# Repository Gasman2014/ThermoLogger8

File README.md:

# ThermoLogger8

Just quickly pushed this repo if anyone is interested. It works in bradboard format and I have designed a PCB in KiCad. There is a 5v and 
a 3.3v version depending on choice of MC. I have been using Fosil as a VCS for this project and have just pushed the whole repo to GitHub.
If you are interested in the development history I could add the Fossil.repo.

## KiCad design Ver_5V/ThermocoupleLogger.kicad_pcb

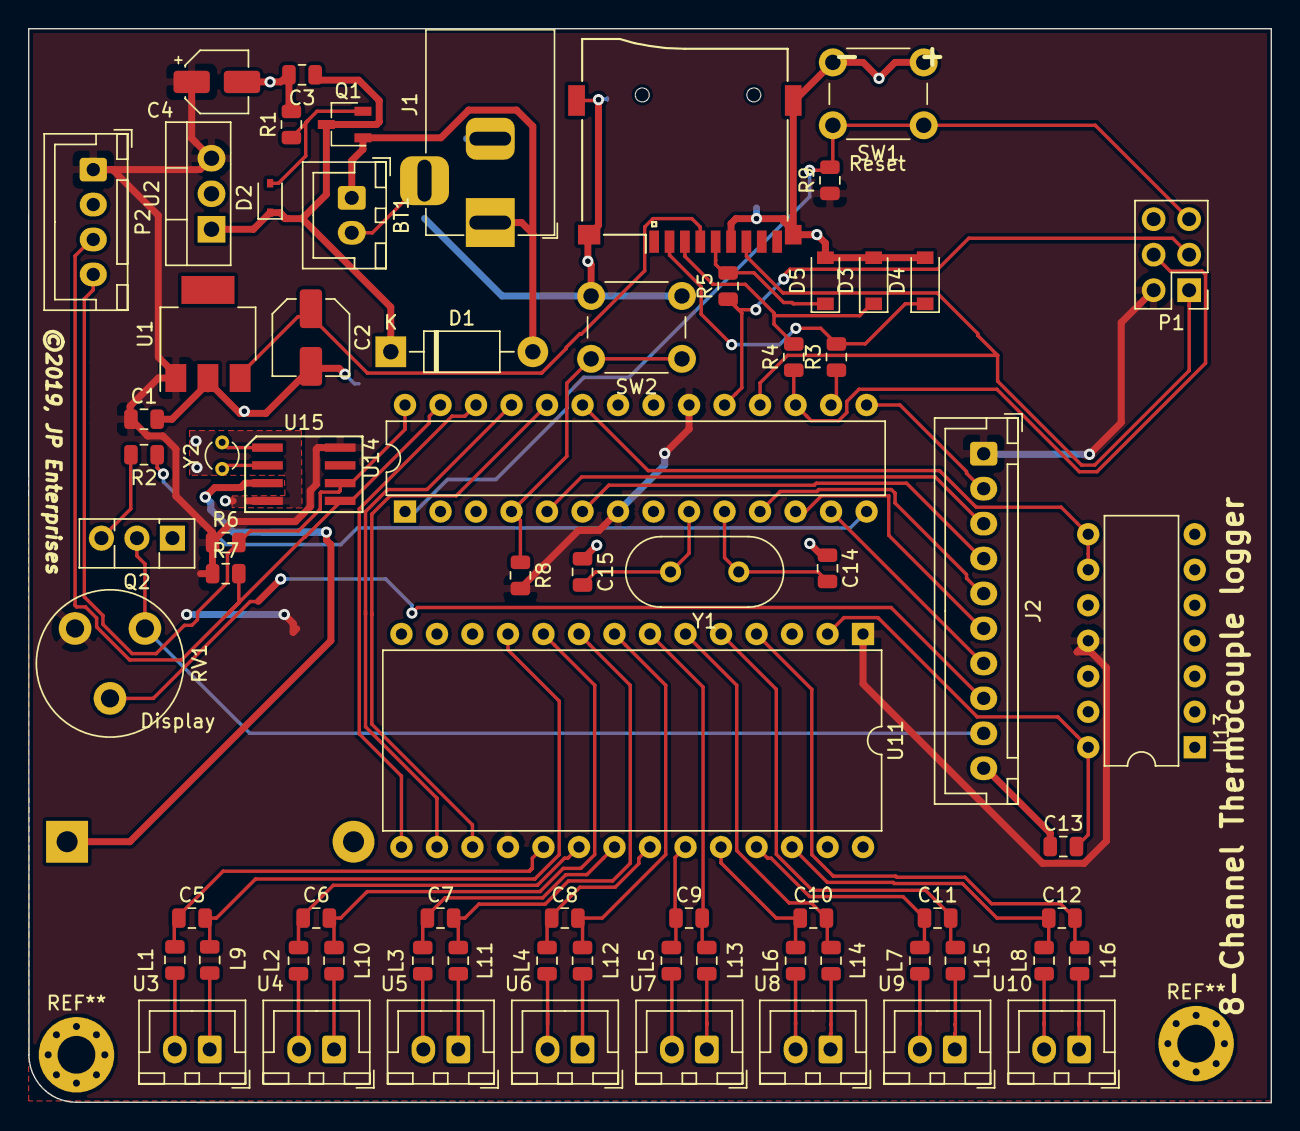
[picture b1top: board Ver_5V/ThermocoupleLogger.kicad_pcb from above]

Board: 2 copper layers, 88.9 x 76.8 mm, 73 parts (1 on the bottom side), 70 nets.

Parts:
BT1: 9V; JST_XH_B02B-XH-A_1x02_P2.50mm_Vertical
BT2: Battery; BatteryHolder_Keystone_103_1x20mm
C1: 470nF; C_0805_2012Metric
C2: 47uF; C_Elec_5x5.4
C3: 1uF; C_0805_2012Metric
C4: 10uF; CP_Elec_4x5.4
C5, C6, C7, C8, C9, C10, C11, C12, C13: 10nF; C_0805_2012Metric
C14, C15: 18pF; C_0805_2012Metric
D1: 1N4007; D_DO-41_SOD81_P10.16mm_Horizontal
D2: 9V; D_SOD-323
D3, D4, D5: 3.3V; D_SOD-123
J1: Barrel_Jack; BarrelJack_Horizontal
J2: Conn_01x12_Male; JST_XH_B10B-XH-A_1x10_P2.50mm_Vertical
L1, L2, L3, L4, L5, L6, L7, L8, L9, L10, L11, L12, L13, L14, L15, L16: 150; L_0805_2012Metric
P1: CONN_02X03; PinHeader_2x03_P2.54mm_Vertical
P2: Conn_01x04; JST_XH_B04B-XH-A_1x04_P2.50mm_Vertical
Q1: BS250; TSOT-23
Q2: BD139; TO-126-3_Vertical
R1, R2, R6, R7, R8, R9: 10K; R_0805_2012Metric
R3, R4, R5: 220R; R_0805_2012Metric
RV1: 5k; Potentiometer_Piher_PT-10-V05_Vertical
SW1, SW2: SW_Push; SW_PUSH_6mm_H5mm
U1: LM3940; SOT-223
U2: 7805; TO-220-3_Vertical
U3, U4, U5, U6, U7, U8, U9, U10: TC_Connector; JST_XH_B02B-XH-A_1x02_P2.50mm_Vertical
U11: ADG407; DIP-28_W15.24mm
U13: AD595; DIP-14_W7.62mm
U14: ATMEGA328P-PU; DIP-28_W7.62mm
U15: DS1307+; DS1307
XS1: SD_ebay-uSD-push/push_SMD; Conn_uSDcard
Y1: 16MHz; Crystal_HC49-U_Vertical
Y2: 32.768kHz; Crystal_DS26_D2.0mm_L6.0mm_Vertical

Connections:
3V3: C2.1, U1.3, XS1.4
5V0: C1.1, C4.1, J2.1, P1.2, P2.1, R6.1, R7.1, R8.2, R9.1, RV1.1, U1.1, U2.3, U11.1, U11.18, U13.11, U14.7, U14.20, U15.8
9V0: C3.1, D1.1, D2.1, Q1.3, U2.1
/Thermocouple connectors/SA1: C5.1, L1.1, U11.19
/Thermocouple connectors/SA2: C6.1, L2.1, U11.20
/Thermocouple connectors/SA3: C7.1, L3.1, U11.21
/Thermocouple connectors/SA4: C8.1, L4.1, U11.22
/Thermocouple connectors/SA5: C9.1, L5.1, U11.23
/Thermocouple connectors/SA6: C10.1, L6.1, U11.24
/Thermocouple connectors/SA7: C11.1, L7.1, U11.25
/Thermocouple connectors/SA8: C12.1, L8.1, U11.26
/Thermocouple connectors/SB1: C5.2, L9.2, U11.11
/Thermocouple connectors/SB2: C6.2, L10.2, U11.10
/Thermocouple connectors/SB3: C7.2, L11.2, U11.9
/Thermocouple connectors/SB4: C8.2, L12.2, U11.8
/Thermocouple connectors/SB5: C9.2, L13.2, U11.7
/Thermocouple connectors/SB6: C10.2, L14.2, U11.6
/Thermocouple connectors/SB7: C11.2, L15.2, U11.5
/Thermocouple connectors/SB8: C12.2, L16.2, U11.4
B_LIGHT: R2.1, U14.14
DB4: J2.4, U14.6
DB5: J2.5, U14.11
DB6: J2.6, U14.12
DB7: J2.7, U14.13
DB_MUX: C13.2, U11.2, U13.14
EN: J2.3, U14.5
GND: BT2.2, C1.2, C2.2, C3.2, C4.2, C13.1, C14.1, C15.1, D3.2, D4.2, D5.2, J1.2, J2.10, P1.6, P2.2, Q2.1, R1.2, SW1.2, SW2.2, U1.2, U2.2, U11.12, U11.28, U13.1, U13.4, U13.7, U13.13, U14.8, U14.22, U15.4, XS1.6
MISO: P1.1, U14.18, XS1.7
MOSI: P1.4, R4.1, U14.17
unnamed: BT1.2, J1.3
unnamed: BT2.1, U15.3
unnamed: C14.2, U14.10, Y1.1
unnamed: C15.2, U14.9, Y1.2
unnamed: D2.2, Q1.2, R1.1
unnamed: D3.1, R4.2, XS1.3
unnamed: D4.1, R3.2, XS1.2
unnamed: D5.1, R5.2, XS1.5
unnamed: J2.8, RV1.2
unnamed: J2.9, Q2.2, RV1.3
unnamed: L1.2, U3.2
unnamed: L2.2, U4.2
unnamed: L3.2, U5.2
unnamed: L4.2, U6.2
unnamed: L5.2, U7.2
unnamed: L6.2, U8.2
unnamed: L7.2, U9.2
unnamed: L8.2, U10.2
unnamed: L9.1, U3.1
unnamed: L10.1, U4.1
unnamed: L11.1, U5.1
unnamed: L12.1, U6.1
unnamed: L13.1, U7.1
unnamed: L14.1, U8.1
unnamed: L15.1, U9.1
unnamed: L16.1, U10.1
unnamed: Q2.3, R2.2
unnamed: U15.1, Y2.2
unnamed: U15.2, Y2.1
RESET: P1.5, R9.2, SW1.1, U14.1
RS: J2.2, U14.15
SCK: P1.3, R5.1, U14.19
SCL: P2.4, R6.2, U14.28, U15.6
SDA: P2.3, R7.2, U14.27, U15.5
SELCT: R8.1, SW2.1, U14.4
SLCT0: U11.17, U14.24
SLCT1: U11.16, U14.25
SLCT2: U11.15, U14.26
SS: R3.1, U14.16
SUPPLY: BT1.1, D1.2, J1.1, Q1.1
TEMP: U13.8, U13.9, U14.23

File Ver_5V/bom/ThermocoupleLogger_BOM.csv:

Component,Description,Part,References,Value,Footprint,Quantity Per PCB,Datasheet,Part#,Placement,Package_ID,Characteristics
1,-,Battery-device,BT1,9V,JST_XH_B02B-XH-A_02x2.50mm_Straight,1,/Users/johnpateman/Dropbox/Components/Datasheets/connectors/eXH.pdf,B2B-XH-A,-,-,-
2,-,Battery_Cell-device,BT2,Battery,Keystone_103_1x20mm-CoinCell,1,,KEYSTONE 103,-,-,-
3,-,C_Small-device,C5 C6 C7 C8 C9 C10 C11 C12 C13,10nF,C_0805,9,,-,-,-,X7R -
4,-,CP_Small,C4,10uF,CP_Elec_4x5.4,1,,EEEFK1C100R,-,-,-
5,-,C_Small-device,C16 C17,12pF,C_0805,2,,-,-,-,-
6,-,C_Small-device,C14 C15,18pF,C_0805,2,,-,-,-,-
7,-,C_Small,C3,1uF,C_0805,1,,-,-,-,-
8,-,C_Small-device,C1,470nF,C_0805,1,,-,-,-,X7R
9,-,CP_Small-device,C2,47uF,CP_Elec_5x5.3,1,,EEEFK1C470UR,-,-,-
10,-,1N4007-diode,D1,1N4007,D_DO-41_SOD81_P10.16mm_Horizontal,1,,1N4007,+V1 -V2,-,-
11,-,D_Zener_Small_ALT-device,D3 D4 D5,3.3V,D_SOD-123,3,/Users/johnpateman/Dropbox/Components/Datasheets/Diodes/BZT52C3V3-7-F.pdf,BZT52C3V3-7-F,-,-,-
12,-,D_Schottky_Small-device,D2,9V,D_SOD-323,1,-,BAT60JFILM,+V2 -V1,-,-
13,-,Barrel_Jack-RESCUE-ThermocoupleLogger,J1,Barrel_Jack,BARREL_JACK,1,,MJ-179PH,-,-,-
14,-,Ferrite_Bead_Small,L1 L2 L3 L4 L5 L6 L7 L8 L9 L10 L11 L12 L13 L14 L15 L16,150,L_0805_2012Metric,16,/Users/johnpateman/Dropbox/Components/Datasheets/ferrite/tdk/fcd7f82f19a65440ec3af90a524c5a0e.pdf,MPZ2012S101A,-,-,-
15,-,Conn_02x03_Odd_Even,P1,CONN_02X03,Pin_Header_Straight_2x03_Pitch2.54mm,1,,75869-131LF,-,-,-
16,-,Conn_01x04,P2,Conn_01x04,JST_XH_B04B-XH-A_1x04_P2.50mm_Vertical,1,~,B4B-XH-A,-,-,-
17,-,BD139-RESCUE-ThermocoupleLogger,Q2,BD139,TO-126_Vertical,1,,BD139,-,-,-
18,-,BS250-RESCUE-ThermocoupleLogger,Q1,BS250,TSOT-23,1,,BS250FTA,+V2 -V1,-,-
19,-,R-device,R1,10K,R_0805,1,/Users/johnpateman/Dropbox/Components/Datasheets/resistor_smd/yageo___phycomp/996acc683d858e9d3728cdae3cb41e84.pdf,-,+V2 -V1,-,-
20,-,R_Small-device,R2 R8,10K,R_0805,2,/Users/johnpateman/Dropbox/Components/Datasheets/resistor_smd/yageo___phycomp/996acc683d858e9d3728cdae3cb41e84.pdf,-,-,-,-
21,-,R_Small-device,R3 R4 R5,220R,R_0805,3,/Users/johnpateman/Dropbox/Components/Datasheets/resistor_smd/yageo___phycomp/996acc683d858e9d3728cdae3cb41e84.pdf,-,-,-,-
22,-,R-device,R6 R7,5.1K,R_0805,2,/Users/johnpateman/Dropbox/Components/Datasheets/resistor_smd/yageo___phycomp/996acc683d858e9d3728cdae3cb41e84.pdf,-,-,-,-
23,-,SW_Push-RESCUE-ThermocoupleLogger,SW1 SW2,SW_Push,SW_PUSH_6mm_h5mm,2,,SKHHAJA010,-,-,-
24,-,7805-jp_components,U2,7805,TO-220_Vertical,1,,LM7805,-,-,-
25,-,AD595-jp_components,U13,AD595,DIP-14_W7.62mm,1,file:///Users/johnpateman/Dropbox/Components/Datasheets/Temperature%20measurement/AD594_595.pdf,AD595CQ,-,CERDIP-14,-
26,-,ADG407-jp_components,U11,ADG407,DIP-28_W15.24mm,1,,ADG407,-,PDIP-28_Wide,-
27,-,ATMEGA328P-PU-atmel,U14,ATMEGA328P-PU,DIP-28_W7.62mm,1,/Users/johnpateman/Dropbox/Components/Datasheets/microcontroller/atmel/atmega168pa-pu.pdf,ATMEGA328P-PU,-,DIP-28,-
28,-,DS1307Z+-jp_components,U15,DS1307+,SOIC-8_3.9x4.9mm_Pitch1.27mm,1,https://datasheets.maximintegrated.com/en/ds/DS1307.pdf,DS1307ZN+,-,-,-
29,-,I2C_20x4_DISPLAY-jp_components,U12,I2C_20x4_DISPLAY,JST_XH_B06B-XH-A_06x2.50mm_Straight,1,,B6B-XH-A,-,-,-
30,-,LM3940-jp_components,U1,LM3940,SOT-223,1,/Users/johnpateman/Dropbox/Components/Datasheets/Regulators/lm3940.pdf,LM3940IMP-3.3,-,-,-
31,-,TC_Connector-jp_components,U3 U4 U5 U6 U7 U8 U9 U10,TC_Connector,JST_XH_B02B-XH-A_02x2.50mm_Straight,8,/Users/johnpateman/Dropbox/Components/Datasheets/connectors/eXH.pdf,B2B-XH-A,-,-,-
32,-,SD_ebay-uSD-push_push_SMD-RESCUE-ThermocoupleLogger-ThermocoupleLogger-rescue,XS1,SD_ebay-uSD-push/push_SMD,Conn_uSDcard,1,/Users/johnpateman/Dropbox/Components/Datasheets/SD_Card/5429_b1.pdf,SD_Card[uSD],-,-,-
33,16MHz Vertical crystal,Crystal-device,Y1,16MHz,Crystal_HC49-U_Vertical,1,,FOXSLF-160-20,-,-,-
34,-,Crystal-device,Y2,32.768kHz,Crystal_Round_d3.0mm_Vertical,1,,AB26T-32.768KHZ,-,-,-





Component Groups:,34
Component Count:,73
Fitted Components:,73
Number of PCBs:,1
Total components:,73
Schematic Version:,1.1
Schematic Date:,2017-02-11
BoM Date:,"Thursday, 29 November 2018 at 19:38:18"
Schematic Source:,/Users/johnpateman/EDA_Workspace/Projects/Thermocouple_datalogger/Ver_5V/ThermocoupleLogger.sch
KiCad Version:,Eeschema (5.0.1-3-g963ef8bb5)

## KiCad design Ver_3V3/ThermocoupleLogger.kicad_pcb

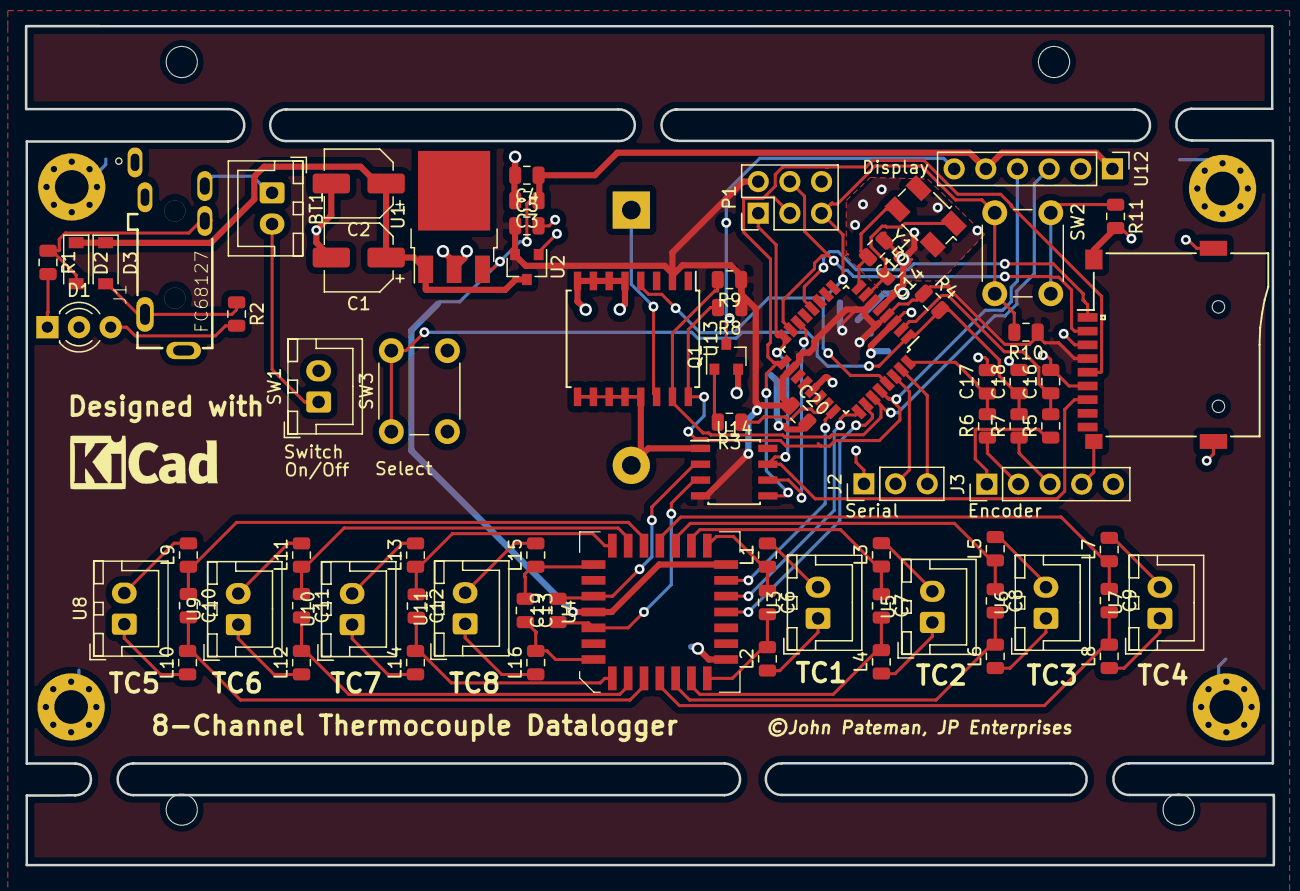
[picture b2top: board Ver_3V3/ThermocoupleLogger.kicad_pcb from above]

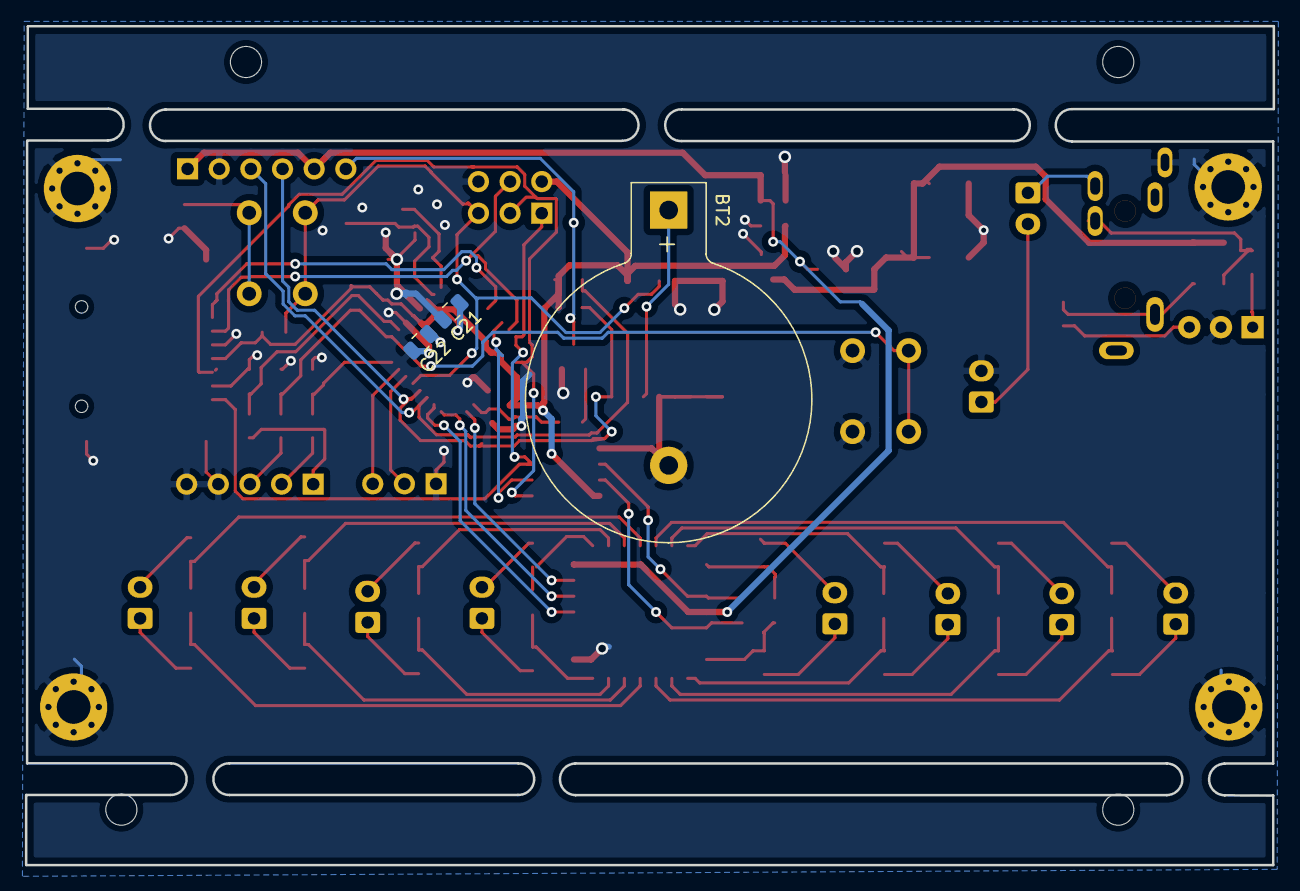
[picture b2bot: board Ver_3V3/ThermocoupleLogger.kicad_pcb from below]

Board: 2 copper layers, 100.1 x 67.3 mm, 87 parts (5 on the bottom side), 70 nets.

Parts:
BT1: Battery; JST_XH_B02B-XH-A_1x02_P2.50mm_Vertical
BT2: 3V [CR2032]; BatteryHolder_Keystone_103_1x20mm
C1, C2: 100uF; CP_Elec_5x5.3
C3, C16, C17, C18, C20, C21, C22: 100nF; C_0805_2012Metric
C4: 10uF; C_0805_2012Metric
C5: 1uF; C_0805_2012Metric
C6, C7, C8, C9, C10, C11, C12, C13, C14, C15, C19: 10nF; C_0805_2012Metric
CON1: SD_Card; Conn_uSDcard
D1: LED_Dual_ACA; LED_D3.0mm-3
D2, D3: 1N4448W-7-F; D_SOD-123
FD1, FD2, FD3, FD4: Alignment_Hole_2.5mm
IC1: ATMEGA328-P; LQFP-32_7x7mm_P0.8mm
J1: FC68127; CLIFF_FC68127
J2: CONN_01X03; PinHeader_1x03_P2.54mm_Vertical
J3: CONN_01X05; PinHeader_1x05_P2.54mm_Vertical
L1, L2, L3, L4, L5, L6, L7, L8, L9, L10, L11, L12, L13, L14, L15, L16: 100 Ohms 10MHz; L_0805_2012Metric
MK1, MK2, MK3, MK4: Mounting_Hole; MountingHole_2.7mm_M2.5_Pad_Via
P1: Conn_02x03_Top_Bottom; PinHeader_2x03_P2.54mm_Vertical
Q1: MMBT3904LT1G; SOT-23
R1, R2: 750R; R_0805_2012Metric
R3, R4, R10: 10k; R_0805_2012Metric
R5, R6, R7: 22k; R_0805_2012Metric
R8, R9: 4.7k; R_0805_2012Metric
R11: 330R; R_0805_2012Metric
SW1: SW_SPST; JST_XH_B02B-XH-A_1x02_P2.50mm_Vertical
SW2, SW3: SW_PUSH; SW_PUSH_6mm_H4.3mm
U1: LF50_TO252; TO-252-3_TabPin4
U2: RT9166-33GVL; SOT-23
U3, U5, U6, U7, U8, U9, U10, U11: TC_Connector; JST_XH_B02B-XH-A_1x02_P2.50mm_Vertical
U4: ADG407BPZ; PLCC-28
U12: I2C_20x4_DISPLAY; Pin_Header_Straight_1x06_Pitch2.54mm
U13: DS3231M; SOIC-16W_7.5x10.3mm_P1.27mm
U14: MAX31855KASA; SOIC-8_3.9x4.9mm_P1.27mm
Y1: Crystal_8MHz; Crystal_SMD_Abracon_ABM3B-4Pin_5.0x3.2mm

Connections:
3V3: C5.1, C20.1, C21.1, C22.1, CON1.4, IC1.4, IC1.6, IC1.18, P1.2, R4.1, R8.1, R9.1, R10.1, U2.2, U13.2, U14.4
5V0: C3.1, C4.1, U1.3, U4.1, U4.18, U12.1, U12.5
9V0: C1.1, C2.1, D2.1, D3.1, U1.1, U2.3
/Thermocouple connectors/SA1: C6.1, L1.1, U4.19
/Thermocouple connectors/SA2: C7.1, L3.1, U4.20
/Thermocouple connectors/SA3: C8.1, L5.1, U4.21
/Thermocouple connectors/SA4: C9.1, L7.1, U4.22
/Thermocouple connectors/SA5: C10.1, L9.1, U4.23
/Thermocouple connectors/SA6: C11.1, L11.1, U4.24
/Thermocouple connectors/SA7: C12.1, L13.1, U4.25
/Thermocouple connectors/SA8: C13.1, L15.1, U4.26
/Thermocouple connectors/SB1: C6.2, L2.2, U4.11
/Thermocouple connectors/SB2: C7.2, L4.2, U4.10
/Thermocouple connectors/SB3: C8.2, L6.2, U4.9
/Thermocouple connectors/SB4: C9.2, L8.2, U4.8
/Thermocouple connectors/SB5: C10.2, L10.2, U4.7
/Thermocouple connectors/SB6: C11.2, L12.2, U4.6
/Thermocouple connectors/SB7: C12.2, L14.2, U4.5
/Thermocouple connectors/SB8: C13.2, L16.2, U4.4
B_LIGHT: IC1.23, R3.1
DA_MUX: C19.2, U4.28, U14.2
DB_MUX: C19.1, U4.2, U14.3
ENC_A: C17.1, IC1.32, R6.2
ENC_B/SW1: C18.1, IC1.1, R4.2, R7.2, SW3.1
ENC_SW: C16.1, IC1.2, R5.2
GND: BT2.2, C1.2, C2.2, C3.2, C4.2, C5.2, C14.1, C15.1, C16.2, C17.2, C18.2, C20.2, C21.2, C22.2, CON1.3, CON1.6, D1.2, IC1.3, IC1.5, IC1.21, J1.1, J2.1, J3.4, J3.5, MK1.1, MK2.1, MK3.1, MK4.1, P1.6, Q1.2, R11.2, SW1.2, SW3.2, U1.2, U2.1, U4.12, U12.2, U13.5, U13.6, U13.7, U13.8, U13.9, U13.10, U13.11, U13.12, U13.13, U14.1, Y1.2, Y1.4
MISO: CON1.7, IC1.16, P1.1, U14.7
MOSI: CON1.2, IC1.15, P1.4
unnamed: BT1.1, J1.4
unnamed: BT1.2, SW1.1
unnamed: BT2.1, U13.14
unnamed: C14.2, IC1.7, Y1.1
unnamed: C15.2, IC1.8, Y1.3
unnamed: D1.1, R1.2
unnamed: D1.3, R2.2
unnamed: D2.2, J1.2, R1.1
unnamed: D3.2, J1.3, R2.1
unnamed: J3.1, R5.1
unnamed: J3.2, R6.1
unnamed: J3.3, R7.1
unnamed: L1.2, U3.2
unnamed: L2.1, U3.1
unnamed: L3.2, U5.2
unnamed: L4.1, U5.1
unnamed: L5.2, U6.2
unnamed: L6.1, U6.1
unnamed: L7.2, U7.2
unnamed: L8.1, U7.1
unnamed: L9.2, U8.2
unnamed: L10.1, U8.1
unnamed: L11.2, U9.2
unnamed: L12.1, U9.1
unnamed: L13.2, U10.2
unnamed: L14.1, U10.1
unnamed: L15.2, U11.2
unnamed: L16.1, U11.1
unnamed: Q1.1, R3.2
unnamed: Q1.3, U12.6
unnamed: R11.1, SW2.2
RESET: IC1.29, P1.5, R10.2, SW2.1, U13.4
Rx: IC1.30, J2.2
SCK: CON1.5, IC1.17, P1.3, U14.5
SCL: IC1.28, R8.2, U12.4, U13.16
SDA: IC1.27, R9.2, U12.3, U13.15
SLCT0: IC1.24, U4.17
SLCT1: IC1.25, U4.16
SLCT2: IC1.26, U4.15
SS0: CON1.1, IC1.12
SS1: IC1.14, U14.6
Tx: IC1.31, J2.3

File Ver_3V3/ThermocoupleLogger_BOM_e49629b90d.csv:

Component,Description,Part,References,Value,Footprint,Quantity Per PCB,Datasheet,Part#,Placement,Package_ID,Characteristics,,C3 C16 C17 C18 C20 C21 C22,100nF 0805,7,C_0805,71,Multiple-cell battery,Battery,BT2,3V [CR2032],Keystone_106_1x20mm-CoinCell,1,,KEYSTONE 103,-,-,-,,C6 C7 C8 C9 C10 C11 C12 C13 C14 C15 C19,10nF 0805,11,C_0805,112,Multiple-cell battery,Battery,BT1,Battery,JST_XH_B02B-XH-A_1x02_P2.50mm_Vertical,1,,B2B-XH-A(LF)(SN),-,-,-,,C4,10uF 0805,1,C_0805,13,"Unpolarized capacitor, small symbol",C_Small,C3 C16 C17 C18 C20 C21 C22,100nF,C_0805,7,,-,-,-,-,,C5,1uF 0805,1,C_0805,14,"Polarized capacitor, small symbol",CP_Small,C1 C2,100uF,CP_Elec_5x5.3,2,,EEEFT1C101AR,-,-,-,,D2 D3,1N4448W-7-F SOD-123,2,D_,25,"Unpolarized capacitor, small symbol",C_Small,C6 C7 C8 C9 C10 C11 C12 C13 C14 C15 C19,10nF,C_0805,11,,-,-,-,-,,IC1,ATMEGA328-P,1,TQFP-32_7x7mm_Pitch0.8mm,16,"Polarized capacitor, small symbol",CP_Small,C4,10uF,C_0805,1,,-,-,-,-,,J1,FC68127,1,CLIFF_FC68127,17,"Unpolarized capacitor, small symbol",C_Small,C5,1uF,C_0805,1,,-,-,-,-,,L1 L2 L3 L4 L5 L6 L7 L8 L9 L10 L11 L12 L13 L14 L15 L16,Ferrite 100 Ohms 10MHz 0805,16,L_0805,168,SD Card Reader,SD_Card,CON1,SD_Card,Conn_uSDcard,1,http://portal.fciconnect.com/Comergent//fci/drawing/10067847.pdf,SD_Card[uSD],-,-,-,,P1,Conn_02x03_Top_Bottom,1,PinHeader_2x03_P2.54mm_Vertical,19,"50V 1A General Purpose Rectifier Diode, DO-41",1N4001,D2 D3,1N4448W-7-F,D_SOD-123,2,http://www.vishay.com/docs/88503/1n4001.pdf,1N4448W-7-F,-,-,-,,Q1,MMBT3904LT1G,1,SOT-23,110,"Dual LED, common cathode on pin 2",LED_Dual_ACA,D1,LED_Dual_ACA,LED_D3.0mm-3,1,,L-93WEGW,-,-,-,,R3 R4 R10,10k,3,R_0805,311,,ATMEGA328P-AU-RESCUE-ThermocoupleLogger,IC1,ATMEGA328-P,TQFP-32_7x7mm_Pitch0.8mm,1,,ATMEGA328P-AU,-,-,-,,R5 R6 R7,22k,3,R_0805,312,"Generic connector, single row, 01x03, script generated (kicad-library-utils/schlib/autogen/connector/)",Conn_01x03,J2,CONN_01X03,Pin_Header_Straight_1x03_Pitch2.54mm,1,,B3B-XH-A(LF)(SN),-,-,-,,R11,330R,1,R_0805,113,"Generic connector, single row, 01x05, script generated (kicad-library-utils/schlib/autogen/connector/)",Conn_01x05,J3,CONN_01X05,PinHeader_1x05_P2.54mm_Vertical,1,,B5B-XH-A(LF)(SN),-,-,-,,R8 R9,4.7k,2,R_0805,214,"Jack socket, 3.5mm, 4-Pole",FC68127,J1,FC68127,CLIFF_FC68127,1,FC68127,FC68127,-,-,-,,R1 R2,750R,2,R_0805,215,"Ferrite bead, small symbol",Ferrite_Bead_Small,L1 L2 L3 L4 L5 L6 L7 L8 L9 L10 L11 L12 L13 L14 L15 L16,100 Ohms 10MHz,L_0805,16,,MPZ2012S101A,-,-,-,,SW2 SW3,SW_PUSH,2,SW_PUSH_6mm_H4.3mm,216,"Generic connector, double row, 02x03, top/bottom pin numbering scheme (row 1: 1...pins_per_row, row2: pins_per_row+1 ... num_pins), script generated (kicad-library-utils/schlib/autogen/connector/)",Conn_02x03_Top_Bottom,P1,Conn_02x03_Top_Bottom,PinHeader_2x03_P2.54mm_Vertical,1,,75869-131LF,-,-,-,,SW1,SW_SPST,1,JST_XH_B02B-XH-A_1x02_P2.50mm_Vertical,117,"0.2A Ic, 40V Vce, Small Signal NPN Transistor, SOT-23",MMBT3904,Q1,MMBT3904LT1G,SOT-23,1,http://www.fairchildsemi.com/ds/BC/BC817.pdf,MMBT3904LT1G,-,-,-,,U4,ADG407BPZ,1,PLCC-28,118,"Resistor, small symbol",R_Small,R3 R4 R10,10k,R_0805,3,,-,-,-,-,,U13,DS3231,1,SOIC-16W_7.5x10.3mm_Pitch1.27mm,119,"Resistor, small symbol",R_Small,R5 R6 R7,22k,R_0805,3,,-,-,-,-,,U1,LF50_TO252,1,TO-252-3_TabPin4,120,"Resistor, small symbol",R_Small,R11,330R,R_0805,1,,-,-,-,-,,U14,MAX31855KASA,1,SOIC-8_3.9x4.9mm_P1.27mm,121,Resistor,R,R8 R9,4.7k,R_0805,2,,-,-,-,-,,U2,RT9166-33GVL,1,SOT-23,122,"Resistor, small symbol",R_Small,R1 R2,750R,R_0805,2,,-,-,-,-,,U3 U5 U6 U7 U8 U9 U10 U11,TC_Connector,8,JST_XH_B02B-XH-A_1x02_P2.50mm_Vertical,823,"Push button switch, generic, two pins",SW_Push,SW2 SW3,SW_PUSH,SW_PUSH_6mm_H4.3mm,2,,SKHHAJA010,-,-,-,,Y1,Crystal_8MHz,1,Crystal_SMD_Abracon_ABM3B-4pin_5.0x3.2mm,124,Single Pole Single Throw (SPST) switch,SW_SPST,SW1,SW_SPST,JST_XH_B02B-XH-A_1x02_P2.50mm_Vertical,1,,B2B-XH-A(LF)(SN),-,-,-,,,,,,25,ADG406/407/426_Analog Multiplexer,ADG407,U4,ADG407BPZ,PLCC-28,1,http://www.analog.com/media/en/technical-documentation/data-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,ADG407BPZ,-,-,-,,,,,,26,,DS3231M,U13,DS3231,SOIC-16W_7.5x10.3mm_Pitch1.27mm,1,,DS3231M+,-,-,-,,,,,,28,,7805-RESCUE-ThermocoupleLogger,U1,LF50_TO252,TO-252-3_TabPin4,1,,LF50ABDT-TR,-,-,-,,,,,,29,"Cold Junction K-type Thermocouple Interface, SPI, SO8",MAX31855KASA,U14,MAX31855KASA,SOIC-8_3.9x4.9mm_P1.27mm,1,http://datasheets.maximintegrated.com/en/ds/MAX31855.pdf,MAX31855KASA,-,-,-,,,,,,30,"Low Quiescent Current LDO Regulator, 3.3V, 250 mA, Vin<=16V, SOT-23",MCP1703A-3302_SOT23,U2,RT9166-33GVL,SOT-23,1,http://ww1.microchip.com/downloads/en/DeviceDoc/20005122B.pdf,RT9166-33GVL,-,-,-,,,,,,31,TC_Connector,TC_Connector,U3 U5 U6 U7 U8 U9 U10 U11,TC_Connector,JST_XH_B02B-XH-A_1x02_P2.50mm_Vertical,8,,B2B-XH-A(LF)(SN),-,-,-,,,,,,32,"Four pin crystal, GND on pins 2 and 4",Crystal_GND24,Y1,Crystal_8MHz,Crystal_SMD_Abracon_ABM3B-4pin_5.0x3.2mm,1,,ABM3B-8.000MHZ-B2-T,,-,-,,,,,,,,,,,,,,,,,,,,,,,,,,,,,,,,,,,,,,,,,,,,,,,,,,,,,,,,,,,,,,,,,,,,,,,,,,,,,,,,,,,,,,,,,,,Component Groups:,32,,,,,,,,,,,,,,,,Component Count:,79,,,,,,,,,,,,,,,,Fitted Components:,79,,,,,,,,,,,,,,,,Number of PCBs:,1,,,,,,,,,,,,,,,,Total components:,79,,,,,,,,,,,,,,,,Schematic Version:,e49629b90d,,,,,,,,,,,,,,,,Schematic Date:,11/06/18,,,,,,,,,,,,,,,,BoM Date:,"Saturday, 01 December 2018 at 09:49:37",,,,,,,,,,,,,,,,Schematic Source:,/Users/johnpateman/EDA_Workspace/Projects/Thermocouple_datalogger/Ver_3V3/ThermocoupleLogger.sch,,,,,,,,,,,,,,,,KiCad Version:,Eeschema (5.0.1-3-g963ef8bb5),,,,,,,,,,,,,,,,

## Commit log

2020-03-25 Added all local design files
2020-03-25 Update README.md
    Added some background info

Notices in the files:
Ver_3V3/ThermocoupleLogger.kicad_pcb:
©John Pateman, JP Enterprises
Ver_5V/ThermocoupleLogger.kicad_pcb:
©2019, JP Enterprises
